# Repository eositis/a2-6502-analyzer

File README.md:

# a2-6502-analyzer
The A2-6502 is an adapter allowing [Dr Gusman's LogicAnalyzer](https://github.com/gusmanb/logicanalyzer) to capture all 6502 signal pins on an Apple II. This adapter is spefically designed for the Apple IIc, but work equally well in the Apple IIe. It will work in the older Apple II and II+, however extra spacers are required, as the expansion slots get in the way.

In the Apple IIc, the adapter fits into the motherboard's CPU socket, even with the motherboard still in the case. No other components are obstructed, giving the user complete access to all available signals on the board. In an Apple IIe, the adapter's layout also allows access to all signals on the system. It does however block the use of slots 3 and 4.

The adapter board maps the Apple IIc 6502 signals to specific ports on the LogicAnalyzer pair. An additional 16 ports are available on an expansion header, allowing the user to not only capture cpu specific signals, but to also reach out to additional areas of the system to gather related information.

Dr Gusman's 6.5 release is recommended for this deployment. At this time, it is still in beta. This release provides profile support, and allows the user to import a port assignment set when using the a2-6502 adapter. A basic profile for this board is available [here](https://github.com/eositis/a2-6502-analyzer/tree/main/Gusmans-LogicAnalyzer).
1. profiles.json
   - MacOS and Linux users copy the file to $HOME/Library/Application Support/LogicAnalyzer
   - Windoze users copy the file to %userprofile%/appdata/roaming/logicanalyzer
   - if you already have a pofile created, you will need to copy the relevant data into your existing profile

## Initial Setup
1) Install firmware to LogicAnalyzer
2) Install two LogicAnalyzer boards to the adapter with the component side facing the cpu
3) Using three DuPont cables, connect the linking headers between the two boards. Does not matter which ports combination is used, as long as top is to top, middle to middle and bottom to bottom.
   - LogicAnalyzers purchased from me will be configured to snap together, eliminating this step.
4) Remve the cpu from the system board, and install it in the provided space on the adapter board. Be sure to maintain the correct notch orientation.
   - Optionally, install a spare CPU in the adapter board, leaving it there permanently. Set aside the system's CPU for the duration of the tests.
6) Carefully plug the adapter board into the cpu socket on the mother board - once again, take care to maintain correct notch orientation. Make sure the adapter is fully seated in the socket.
   - Some older sockets may not have sufficiently large holes for the logic analyzer's pins. If this is the case, install a doublewipe cpu socket to the motherboard and plug the logic analyzer adapter board into the doublewipe socket.
8) Download and configure the LogicAnalyzer software
   - Stable release here: https://github.com/gusmanb/logicanalyzer/releases
   - 6.5 beta realease information is here: https://github.com/gusmanb/logicanalyzer/discussions/277
10) follow install and operation guidelines in the [LogicAnalyzer wiki](https://github.com/gusmanb/logicanalyzer/wiki/06---The-LogicAnalyzer-program)

### Setup LogicAnalyzer boards using USB
1) Two USB cables will be needed
2) On the adapter board, set the jumper/switch to USB mode.
   - WiFi mode should only be used when the LogicAnalyzer has been configured for Network operation running in full wireless mode.
3) On each LogicAnalyzer board is a switch to set reference voltage
   - Typically should be set to EXT mode. This will use the Apple II system's 5v rail as a reference
   - The 5V reference can also be used. This mode can be used if testing Apple II power-on procedures. Testers have suggested that the LogicAnalyzer should start up faster than the Apple II, however this has not been confirmed.
4) Install firmware
   - extract the firmware appropriate for the Pico board installed on the LogicAnalyzers. This firmware is a part of the comprehensive download performed in an earlier step
   - each Pico board has a small reset button. Hold down this button wile plugging in one of the USB cables. Repeat for the other board.
   - on your computer, two new USB volumes will appear. Copy the appropriate firmware to the storage volume. Immediately once the copy completes, the volume will disconnect from your computer and the LogicAnalyzer will reset and boot the new firmware.
5) Configure for use
   - Start the LogicAnalyzer software
   - connect USB cables to each of the logic analyzers
   - Configure a MultiDevice scanner
   - Click 'open device'
   - Select one of the LogicAnalyzer boards as master
   - Add the second one as slave, Accept
   - Execute a data capture from an Apple II machine, do add signals via the J3 port at this time
   - Channels up to  32 should have data. Channels 33-48 should be blank lines. If this is not the case, close the device and recreate it, placing the other LogicAnalyzer as master.
   - From the profiles menu, select the previously imported Apple II profile
6) Congratulations! Setup is complete!

## Channel assignments
| J1-Analyzer1 | Signal | Pin | J2-Analyzer2 | Signal |
|-------------:|--------|---|-------------:|--------|
| CH-1 | RDY | 1 | CH-25 | A8 |
| CH-2 | IRQ\ | 2 | CH-26 | A9 |
| CH-3 | NMI\ | 3 | CH-27 | A10 |
| CH-4 | R/W\ | 4 | CH-28 | A11 |
| CH-5 | PHASE0 | 5 | CH-29 | A12 |
| CH-6 | RES\ | 6 | CH-30 | A13 |
| CH-7 | D0 | 7 | CH-31 | A14 |
| CH-8 | D1 | 8 | CH-32 | A15 |
| CH-9 | D2 | 9 | CH-33 | J3-1 |
| CH-10 | D3 | 10 | CH-34 | J3-2 |
| CH-11 | D4 | 11 | CH-35 | J3-3 |
| CH-12 | D5 | 12 | CH-36 | J3-4 |
| CH-13 | D6 | 21 | CH-37 | J3-5 |
| CH-14 | D7 | 22 | CH-38 | J3-6 |
| CH-15 | A1 | 23 | CH-39 | J3-7 |
| CH-16 | A2 | 24 | CH-40 | J3-8 |
| CH-17 | A3 | 25 | CH-41 | J3-9 |
| CH-18 | A4 | 26 | CH-42 | J3-10 |
| CH-19 | A5 | 27 | CH-43 | J3-11 |
| CH-20 | A6 | 28 | CH-44 | J3-12 |
| CH-21 | A7 | 29 | CH-45 | J3-13 |
| CH-22 | A8 | 30 | CH-46 | J3-14 |
| CH-23 | Phase1 | 32 | CH-47 | J3-15 |
| CH-24 | SYNC | 32 | CH-48 | J3-16 |

## J3 header pin assignments
The Opt X.nn signals are routed to the J3 breakout header. The user can use standard DuPont cables and clips to reach out to other parts of the system for additional data.
The J3 header signals are ordered as follows:

| PIN-1 | PIN-3 | PIN-5 | PIN-7 | PIN-9 | PIN-11 | PIN-13 | PIN-15 |
|:-----:|:-----:|:-----:|:-----:|:-----:|:-----:|:-----:|:-----:|
| CH-33 | CH-35 | CH-37 | CH-39 | CH-41 | CH-43 | CH-45 | CH-47 |
| CH-34 | CH-36 | CH-38 | CH-40 | CH-42 | CH-44 | CH-46 | CH-48 |
| PIN-2 | PIN-4 | PIN-6 | PIN-8 | PIN-10 | PIN-12 | PIN-14 | PIN-16 |

## Schematics
Production v1.5 schematic: https://github.com/eositis/a2-6502-analyzer/blob/main/kicad/v1.5/6502-interposer-schematic-1_5.pdf

### Board View

### Ready to collect data

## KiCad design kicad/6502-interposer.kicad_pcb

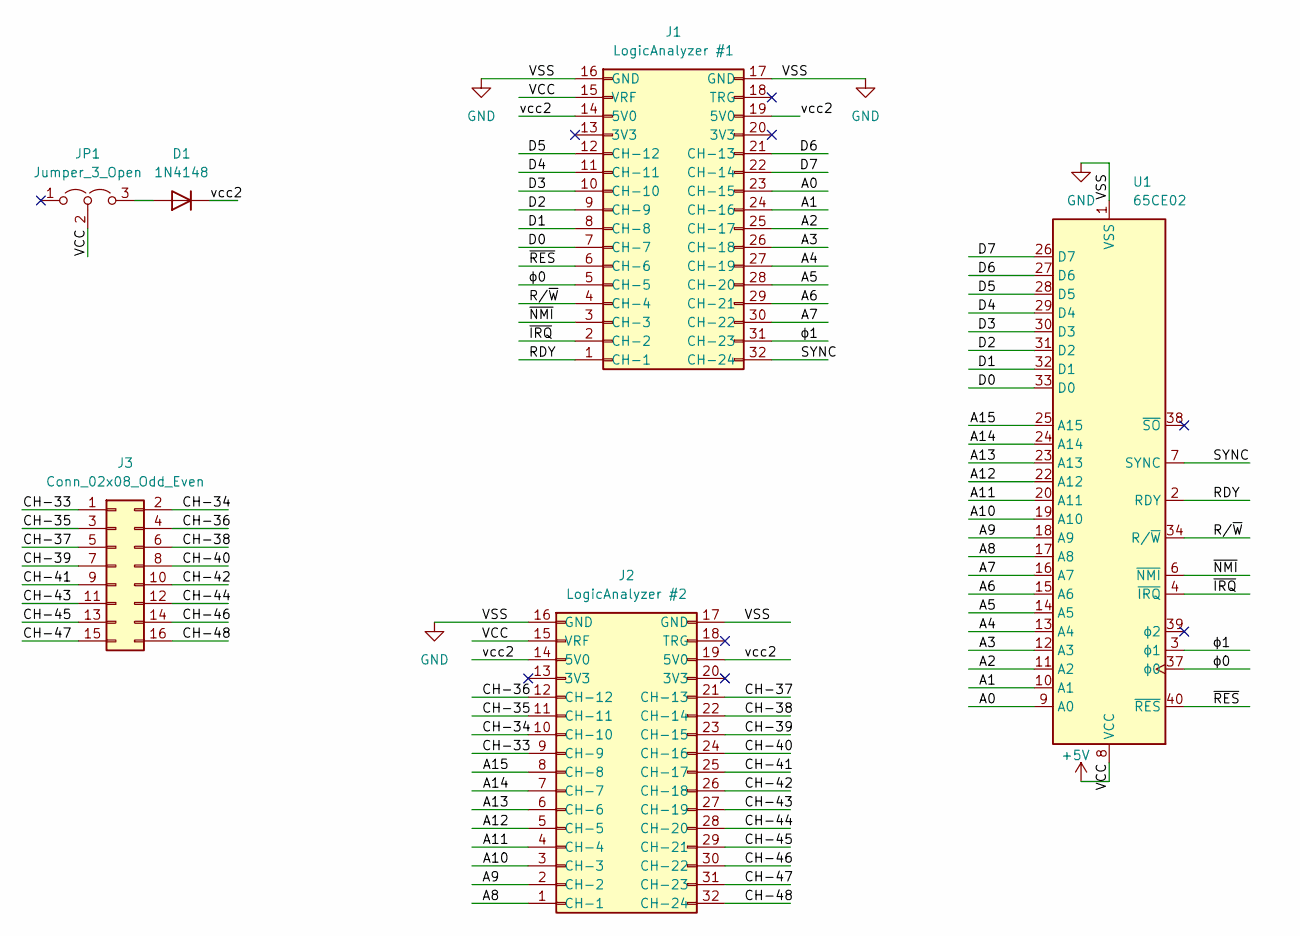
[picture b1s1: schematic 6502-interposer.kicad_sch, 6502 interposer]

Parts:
D1: 1N4148; D_DO-35_SOD27_P7.62mm_Horizontal
J1: LogicAnalyzer #1; PinSocket_2x16_P2.54mm_Vertical
J2: LogicAnalyzer #2; PinSocket_2x16_P2.54mm_Vertical
J3: Conn_02x08_Odd_Even; PinSocket_2x08_P2.54mm_Vertical
JP1: Jumper_3_Open; PinHeader_1x03_P2.54mm_Vertical
U1: 65CE02; DIP-40_W15.24mm

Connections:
+5V: J1.15 (VRF), J2.15 (VRF), JP1.2 (C), U1.8 (VCC)
/A0: J1.23 (CH-15), U1.9 (A0)
/A1: J1.24 (CH-16), U1.10 (A1)
/A2: J1.25 (CH-17), U1.11 (A2)
/A3: J1.26 (CH-18), U1.12 (A3)
/A4: J1.27 (CH-19), U1.13 (A4)
/A5: J1.28 (CH-20), U1.14 (A5)
/A6: J1.29 (CH-21), U1.15 (A6)
/A7: J1.30 (CH-22), U1.16 (A7)
/A8: J2.1 (CH-1), U1.17 (A8)
/A9: J2.2 (CH-2), U1.18 (A9)
/A10: J2.3 (CH-3), U1.19 (A10)
/A11: J2.4 (CH-4), U1.20 (A11)
/A12: J2.5 (CH-5), U1.22 (A12)
/A13: J2.6 (CH-6), U1.23 (A13)
/A14: J2.7 (CH-7), U1.24 (A14)
/A15: J2.8 (CH-8), U1.25 (A15)
/CH-33: J2.9 (CH-9), J3.1
/CH-34: J2.10 (CH-10), J3.2
/CH-35: J2.11 (CH-11), J3.3
/CH-36: J2.12 (CH-12), J3.4
/CH-37: J2.21 (CH-13), J3.5
/CH-38: J2.22 (CH-14), J3.6
/CH-39: J2.23 (CH-15), J3.7
/CH-40: J2.24 (CH-16), J3.8
/CH-41: J2.25 (CH-17), J3.9
/CH-42: J2.26 (CH-18), J3.10
/CH-43: J2.27 (CH-19), J3.11
/CH-44: J2.28 (CH-20), J3.12
/CH-45: J2.29 (CH-21), J3.13
/CH-46: J2.30 (CH-22), J3.14
/CH-47: J2.31 (CH-23), J3.15
/CH-48: J2.32 (CH-24), J3.16
/D0: J1.7 (CH-7), U1.33 (D0)
/D1: J1.8 (CH-8), U1.32 (D1)
/D2: J1.9 (CH-9), U1.31 (D2)
/D3: J1.10 (CH-10), U1.30 (D3)
/D4: J1.11 (CH-11), U1.29 (D4)
/D5: J1.12 (CH-12), U1.28 (D5)
/D6: J1.21 (CH-13), U1.27 (D6)
/D7: J1.22 (CH-14), U1.26 (D7)
/RDY: J1.1 (CH-1), U1.2 (RDY)
/R/~W: J1.4 (CH-4), U1.34 (R/~W)
/SYNC: J1.32 (CH-24), U1.7 (SYNC)
/vcc2: D1.1 (K), J1.14 (5V0), J1.19 (5V0), J2.14 (5V0), J2.19 (5V0)
/~IRQ: J1.2 (CH-2), U1.4 (~IRQ)
/~NMI: J1.3 (CH-3), U1.6 (~NMI)
/~RES: J1.6 (CH-6), U1.40 (~RES)
/ϕ0: J1.5 (CH-5), U1.37 (ϕ0)
/ϕ1: J1.31 (CH-23), U1.3 (ϕ1)
GND: J1.16 (GND), J1.17 (GND), J2.16 (GND), J2.17 (GND), U1.1 (VSS), U1.21 (VSS)
unnamed: D1.2 (A), JP1.3 (B)

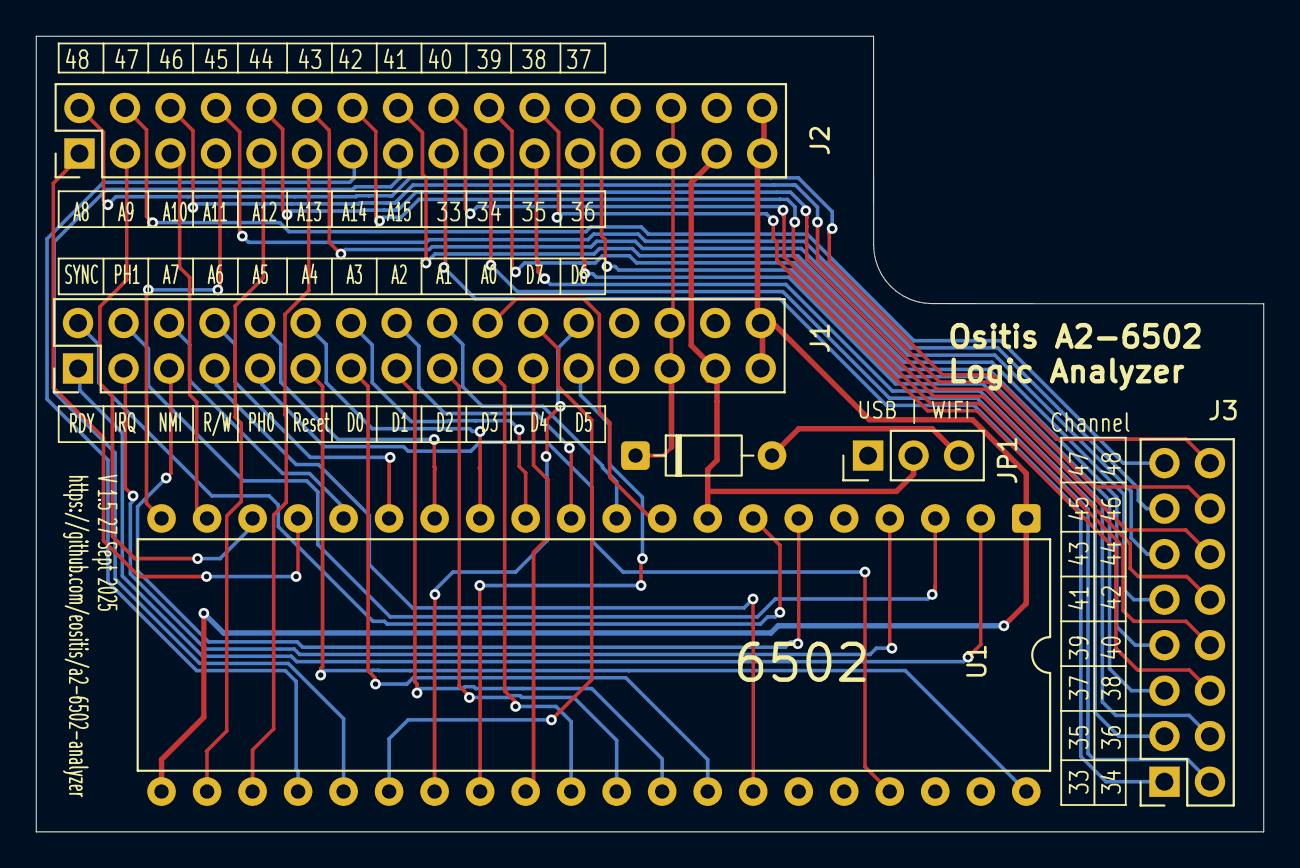
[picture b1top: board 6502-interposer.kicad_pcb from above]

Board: 2 copper layers, 68.5 x 44.4 mm, 6 parts (0 on the bottom side), 52 nets.

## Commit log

2025-09-11 Initial Commit for v1.4
2025-09-11 BOM update
2025-09-11 BOM update2
2025-09-12 version 1.5
    Fix board labelling issues. Fix Numbering issues.
2025-09-18 LogicAnalyzer config files for 6.5beta
2025-09-19 updates for v1.5
2025-09-19 LogicAnalyzer config files added
2025-09-19 cleanup
2025-09-21 repo cleanup and 1.5 update
    cleaned up and reorganized the repository. Updated the 1.5 version to latest, hopefully production version.
2025-09-21 demo pics added
2025-09-21 cleanup unused files
2025-09-21 final cleanup
2025-09-22 Delete a2-6502 manual.pages
    manual is now in the Readme.md doc
2025-09-22 Added Phase1 and SYNC
    Ended up digging into the 6502 documentation to understand why SYNC and Phase1 are important. Although the IIc and IIe do not use these signals, they do have a function. Sync tells us when the cpu is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
2025-09-24 publish errata for 1.4 revision
    bodge wires needed to enable sync and Phase1 capture. This change makes the board compatible with the mos6502 decoder in the LogicAnalyzer 6.5 release
2025-09-24 updating profiles to include sync support
2025-09-24 updating config procedures
2025-09-27 fixed labels, sync routing
2025-09-29 Update profiles.json
    fixing Sync and phase1 location info
